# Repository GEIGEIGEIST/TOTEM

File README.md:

<picture align="center">
  <source media="(prefers-color-scheme: dark)" srcset="/docs/images/TOTEM_logo_dark.svg">
  <source media="(prefers-color-scheme: light)" srcset="/docs/images/TOTEM_logo_bright.svg">
  
</picture>

<h1 align="center">T O T E M</h1>

TOTEM is a 38 key column-staggered choc split keyboard. It is meant to be used with:
- **PCB v0.3:** [Seeed Studio XIAO nRF52840 BLE](https://www.seeedstudio.com/Seeed-XIAO-BLE-nRF52840-p-5201.html) or [XIAO RP2040](https://www.seeedstudio.com/XIAO-RP2040-v1-0-p-5026.html)
- **PCB v0.4:** [Seeed Studio XIAO nRF52840 BLE Plus](https://www.seeedstudio.com/Seeed-Studio-XIAO-nRF52840-Plus-p-6359.html) or [XIAO RP2350](https://www.seeedstudio.com/Seeed-XIAO-RP2350-p-5944.html)

It was created for the SEEED XIAO keyboard contest.\
[Here](https://www.hackster.io/geist/totem-a-tiny-splitkeyboard-with-splay-cb2e43) you can read about the process of making it.

***

## LAYOUT

***

## PCB

[Here](/PCB/) you can find the KiCad files and Gerbers for the TOTEM.

***

## CASE

You can use the TOTEM without a case, but [here](/case/) you can find one I made for it.

***

## BUILD GUIDE

The build guide for the TOTEM can be found [here](/docs/buildguide.md).

***

## FIRMWARE

[QMK (VIAL) precompiled](/firmware/QMK/) or [QMK (VIAL) source](/firmware/QMK/VIAL_source/) for the TOTEM (wired using the XIAO RP2040)\
[ZMK precompiled](/firmware/ZMK/) or [ZMK source (outdated)](https://github.com/GEIGEIGEIST/zmk-config-totem) for the TOTEM (wireless using the XIAO BLE)

***

## BUY

You can buy TOTEM kits and finished builds on [keeb.supply](https://keeb.supply/products/geist-totem) (based in Germany)

***

## PHOTOS

This is the TOTEM in a black resin case

\
\

This is the TOTEM with a black resin tenting bottom plate

\
[Video by *Wolfgang's Channel* showing the tenting system in action](https://youtu.be/rvM2BthjEI4?si=mTJVdPeZstshnDyo)

***

## CREDITS

### INSPIRATION

I've added the additional pinky key to make the TOTEM compatible with the layout boards like the [Balbuzard](https://github.com/brow/balbuzard) by [Tom Brow](https://github.com/brow) and the [Osprette](https://github.com/smores56/osprette) by [Sam Mohr](https://github.com/smores56) use, where you put the keybinding of the top left and right keys on an outer pinky key.

### HELP FIXING THINGS

People who helped me create this board and fix stuff

#### PCB
- [Marco "Bob"](https://github.com/GroooveBob)

#### CASE
- [Freya](https://github.com/freya-irl)
- [Bubbleology](https://github.com/bubbleology)

#### FIRMWARE
- [Cem Aksoylar](https://github.com/caksoylar)
- [Grinnie](https://github.com/regicidalplutophage)
- [Alaa Saad Mansour](https://github.com/AlaaSaadAbdo)
- [pekudzu](https://github.com/pekudzu)

If you build a TOTEM I would be pretty happy to see some pictures. And if you want to leave me a tip you can do this [here](https://ko-fi.com/geigeigeist) (but please don't feel pressured)

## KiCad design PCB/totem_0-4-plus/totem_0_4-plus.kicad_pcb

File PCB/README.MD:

# TOTEM PCB FILES

## MANUFACTURING

There are two versions available. Both fit the same [case](/case/README.MD), but require different microcontrollers.

### Version 0.3 (Standard)
Recommended for the standard **Seeed XIAO nRF52840** or **XIAO RP2040**.
- Download: [totem_0-3_gerbers.zip](/PCB/totem_0-3/totem_0-3_gerbers.zip/)

### Version 0.4 (Plus)
Tailored for the **Seeed XIAO nRF52840 Plus** and **XIAO RP2350**.
This version is **easier to solder** since there is a larger cutout. Also, the **battery pins are farther away** from the keyboard matrix pins, which should avoid shorts.
- Download: [totem_0-4-plus_gerbers.zip](/PCB/totem_0-4-plus/totem_0-4-plus_gerbers.zip)

---

If you want to get the PCB made you need to download the ZIP for your version and upload it to the website of the manufacture.
I can recommend [JLCPCB](https://jlcpcb.com/), [Seeed Fusion](https://www.seeedstudio.com/fusion_pcb.html) or [PCBway](https://www.pcbway.com/).
If you want the silkscreen in yellow [AllPCB](https://www.allpcb.com/online_pcb_quote_new.html) is a pretty affordable choice.

- download the ZIP file for your version
- upload the ZIP file to the website of the manufacturer.
- sometimes the Gerber preview from JLCPCB can't display the PCB, even when the files are fine. In this case use these dimensions: 258.7mm * 94.35mm
- PCB Thickness 1.6mm
- 2 layers
- PCB Qty as much as you like. One PCB is a full keyboard.
- PCB Color Black (or any other color you like)
- No impedance control
- Surface Finish HASL(with lead) if you want the easiest soldering experience or LeadFree HASL.
- Remove Order Number Yes

***

## CHECK PINOUT OR TRACES

If you only want to check the traces or see what is connected to which pin you can take a look at these graphics.
You can also take a look at the PDFs:
- **0.3:** [schematics](TOTEM_0-3_schematics.pdf) and [PCB](TOTEM_0-3_PCB.pdf)
- **0.4:** [schematics](TOTEM_0-3_schematics.pdf) and [PCB](TOTEM_0-4-plus-PCB.pdf)

***

***

## TAKE A DEEPER LOOK OR MODIFY 

You can download the project if you need to take a deeper look or modify something. You need the Open Source software [KiCad](https://www.kicad.org/) to open it.

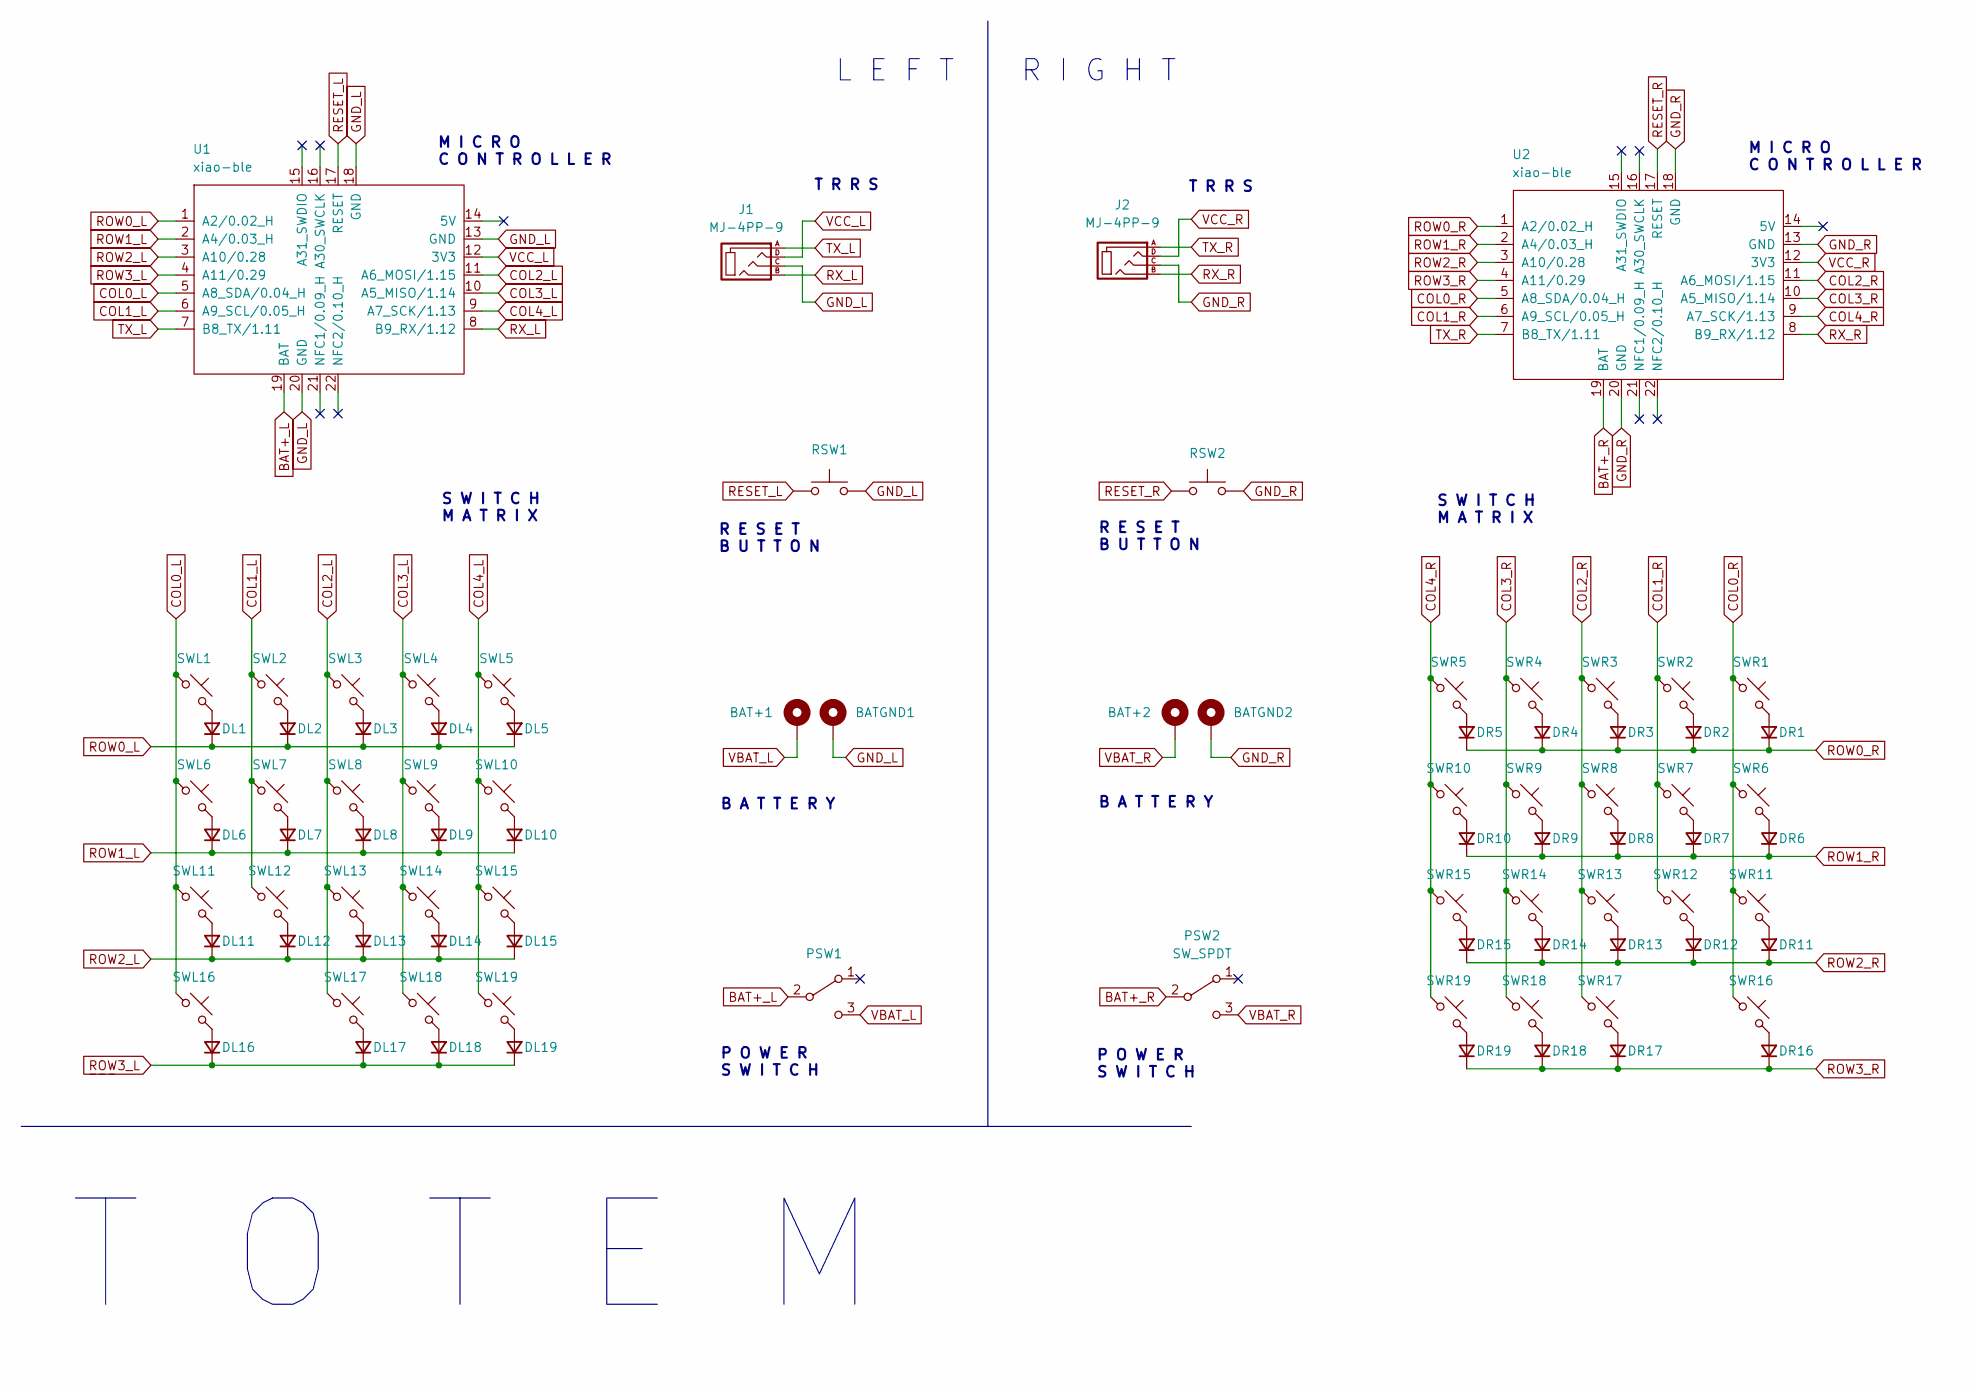
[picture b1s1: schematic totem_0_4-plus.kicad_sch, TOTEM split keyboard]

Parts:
BAT+1, BAT+2: +; BatteryPad
BATGND1, BATGND2: -; BatteryPad
DL1, DL2, DL3, DL4, DL5, DL6, DL7, DL8, DL9, DL10, DL11, DL12, DL13, DL14, DL15, DL16, DL17, DL18, DL19: D_Small; Diode_SOD123
DR1, DR2, DR3, DR4, DR5, DR6, DR7, DR8, DR9, DR10, DR11, DR12, DR13, DR14, DR15, DR16, DR17, DR18, DR19: D_Small; Diode_SOD123
J1, J2: MJ-4PP-9; MJ-4PP-9_1side
PSW1, PSW2: SW_SPDT; MSK12C02
RSW1, RSW2: SW_Push; SKHLLCA010
SWL1, SWL2, SWL3, SWL4, SWL5, SWL6, SWL7, SWL8, SWL9, SWL10, SWL11, SWL12, SWL13, SWL14, SWL15, SWL16, SWL17, SWL18, SWL19: SW_Push_45deg; Kailh_socket_PG1350_optional
SWR1, SWR2, SWR3, SWR4, SWR5, SWR6, SWR7, SWR8, SWR9, SWR10, SWR11, SWR12, SWR13, SWR14, SWR15, SWR16, SWR17, SWR18, SWR19: SW_Push_45deg; Kailh_socket_PG1350_optional
U1, U2: xiao-ble; XIAO-ble-plus

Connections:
BAT+_L: PSW1.2 (B), U1.19 (BAT)
BAT+_R: PSW2.2 (B), U2.19 (BAT)
COL0_L: SWL1.1, SWL6.1, SWL11.1, SWL16.1, U1.5 (A8_SDA/0.04_H)
COL0_R: SWR1.1, SWR6.1, SWR11.1, SWR16.1, U2.5 (A8_SDA/0.04_H)
COL1_L: SWL2.1, SWL7.1, SWL12.1, U1.6 (A9_SCL/0.05_H)
COL1_R: SWR2.1, SWR7.1, SWR12.1, U2.6 (A9_SCL/0.05_H)
COL2_L: SWL3.1, SWL8.1, SWL13.1, SWL17.1, U1.11 (A6_MOSI/1.15)
COL2_R: SWR3.1, SWR8.1, SWR13.1, SWR17.1, U2.11 (A6_MOSI/1.15)
COL3_L: SWL4.1, SWL9.1, SWL14.1, SWL18.1, U1.10 (A5_MISO/1.14)
COL3_R: SWR4.1, SWR9.1, SWR14.1, SWR18.1, U2.10 (A5_MISO/1.14)
COL4_L: SWL5.1, SWL10.1, SWL15.1, SWL19.1, U1.9 (A7_SCK/1.13)
COL4_R: SWR5.1, SWR10.1, SWR15.1, SWR19.1, U2.9 (A7_SCK/1.13)
GND_L: BATGND1.1 (1_1), J1.C, RSW1.2, U1.13 (GND), U1.18 (GND), U1.20 (GND)
GND_R: BATGND2.1 (1_1), J2.C, RSW2.2, U2.13 (GND), U2.18 (GND), U2.20 (GND)
unnamed: DL1.2 (A), SWL1.2
unnamed: DL2.2 (A), SWL2.2
unnamed: DL3.2 (A), SWL3.2
unnamed: DL4.2 (A), SWL4.2
unnamed: DL5.2 (A), SWL5.2
unnamed: DL6.2 (A), SWL6.2
unnamed: DL7.2 (A), SWL7.2
unnamed: DL8.2 (A), SWL8.2
unnamed: DL9.2 (A), SWL9.2
unnamed: DL10.2 (A), SWL10.2
unnamed: DL11.2 (A), SWL11.2
unnamed: DL12.2 (A), SWL12.2
unnamed: DL13.2 (A), SWL13.2
unnamed: DL14.2 (A), SWL14.2
unnamed: DL15.2 (A), SWL15.2
unnamed: DL16.2 (A), SWL16.2
unnamed: DL17.2 (A), SWL17.2
unnamed: DL18.2 (A), SWL18.2
unnamed: DL19.2 (A), SWL19.2
unnamed: DR1.2 (A), SWR1.2
unnamed: DR2.2 (A), SWR2.2
unnamed: DR3.2 (A), SWR3.2
unnamed: DR4.2 (A), SWR4.2
unnamed: DR5.2 (A), SWR5.2
unnamed: DR6.2 (A), SWR6.2
unnamed: DR7.2 (A), SWR7.2
unnamed: DR8.2 (A), SWR8.2
unnamed: DR9.2 (A), SWR9.2
unnamed: DR10.2 (A), SWR10.2
unnamed: DR11.2 (A), SWR11.2
unnamed: DR12.2 (A), SWR12.2
unnamed: DR13.2 (A), SWR13.2
unnamed: DR14.2 (A), SWR14.2
unnamed: DR15.2 (A), SWR15.2
unnamed: DR16.2 (A), SWR16.2
unnamed: DR17.2 (A), SWR17.2
unnamed: DR18.2 (A), SWR18.2
unnamed: DR19.2 (A), SWR19.2
RESET_L: RSW1.1, U1.17 (RESET)
RESET_R: RSW2.1, U2.17 (RESET)
ROW0_L: DL1.1 (K), DL2.1 (K), DL3.1 (K), DL4.1 (K), DL5.1 (K), U1.1 (A2/0.02_H)
ROW0_R: DR1.1 (K), DR2.1 (K), DR3.1 (K), DR4.1 (K), DR5.1 (K), U2.1 (A2/0.02_H)
ROW1_L: DL6.1 (K), DL7.1 (K), DL8.1 (K), DL9.1 (K), DL10.1 (K), U1.2 (A4/0.03_H)
ROW1_R: DR6.1 (K), DR7.1 (K), DR8.1 (K), DR9.1 (K), DR10.1 (K), U2.2 (A4/0.03_H)
ROW2_L: DL11.1 (K), DL12.1 (K), DL13.1 (K), DL14.1 (K), DL15.1 (K), U1.3 (A10/0.28)
ROW2_R: DR11.1 (K), DR12.1 (K), DR13.1 (K), DR14.1 (K), DR15.1 (K), U2.3 (A10/0.28)
ROW3_L: DL16.1 (K), DL17.1 (K), DL18.1 (K), DL19.1 (K), U1.4 (A11/0.29)
ROW3_R: DR16.1 (K), DR17.1 (K), DR18.1 (K), DR19.1 (K), U2.4 (A11/0.29)
RX_L: J1.B, U1.8 (B9_RX/1.12)
RX_R: J2.B, U2.8 (B9_RX/1.12)
TX_L: J1.A, U1.7 (B8_TX/1.11)
TX_R: J2.A, U2.7 (B8_TX/1.11)
VBAT_L: BAT+1.1 (1_1), PSW1.3 (C)
VBAT_R: BAT+2.1 (1_1), PSW2.3 (C)
VCC_L: J1.D, U1.12 (3V3)
VCC_R: J2.D, U2.12 (3V3)

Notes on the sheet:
M I C R O C O N T R O L L E R
T R R S
R E S E T B U T T O N
S W I T C H M A T R I X
P O W E R S W I T C H
T O T E M
B A T T E R Y
R I G H T
L E F T

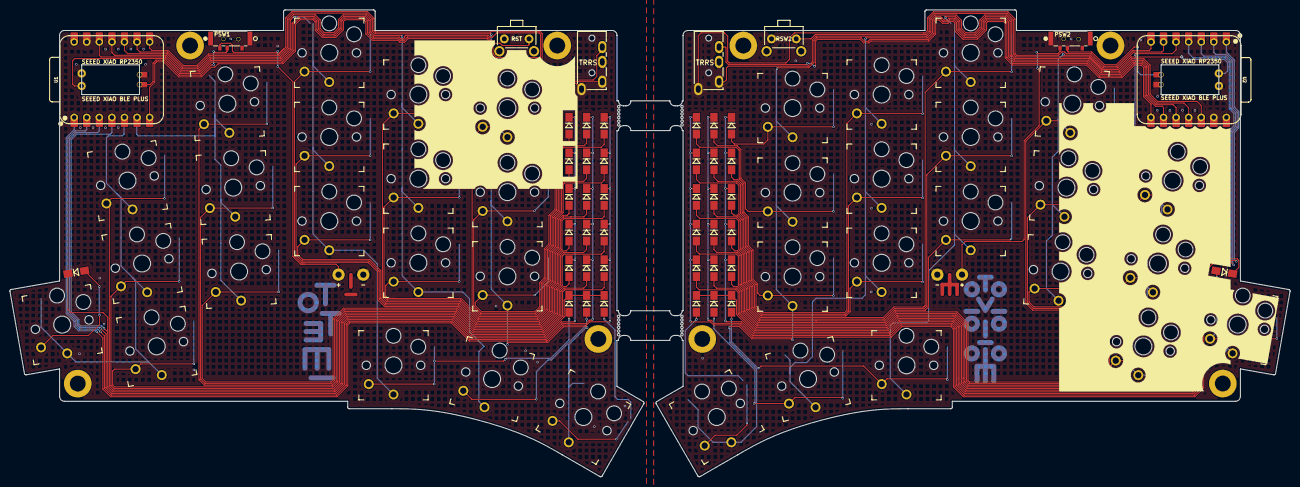
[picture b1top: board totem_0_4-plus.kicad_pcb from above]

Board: 2 copper layers, 258.7 x 94.4 mm, 88 parts (0 on the bottom side), 70 nets.

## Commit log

2022-07-28 update logo
2022-11-03 Update layout
2022-11-03 case render
2022-11-03 buildguide
2022-11-04 add photos
2022-11-04 update photo
2022-11-04 readme
2022-11-04 readmes
2022-11-04 case images
2022-11-04 case documentation
2022-11-04 add case files
2022-11-06 update traces
2022-11-06 layout
2022-11-07 update buildguide
2022-11-10 schematic and PCB as PDF
2022-11-10 Add KiCad files and gerbers
2022-11-13 add case options
2022-12-12 Fixed small typographical error
    without TRRS cutout == wireless version, not wired.
2022-12-20 update case files
2023-04-14 Fix grammar
    Language r hard
2023-05-17 TOTEMX 0.1
    Hello.
    Can be useful. Totally untested.
    Stay safe.
2024-05-21 added tenting case options
2024-05-22 added pictures to main readme
2024-05-22 added more info and pictures to the case readme
2024-05-22 fixed typo and improved linkage
2024-06-01 added usb tenting bottom plate
2024-06-01 removed top piece from stl bottom plates
2024-06-01 renamed usb bottom plate stl file
2024-09-25 Update TOTEM_traces.svg: Add Missing Diode numbers
2024-09-25 Update README.md
    added link to wolfgang's video
2024-10-13 add precompiled firmware
2024-11-01 Remove TRRS & add USB C port to case
2024-11-01 Fillet sharp outer edges of top cases
2024-11-01 Remove TRRS connector indents from BLE bottom cases
2024-11-13 Update buildguide.md
    Update product name to align with the new name on the manufacture's website, adding hyperlinks for people who want to learn more details
2024-11-13 Update README.md
    Update the product name to align with the new name from the manufacture, adding hyperlinks for people who want to explore more
2024-12-08 fix standoff hole near the RST button (9mm)
2024-12-08 update readme on availability
2024-12-08 add VIAL source
2024-12-08 fix video link
2024-12-08 Remove outdated qmk version
2024-12-28 Create a hybrid case with both ble and usb component holes
2024-12-31 Update rules.mk
    Added: SPLIT_KEYBOARD = yes
2025-03-12 Update README.md
    Clarify shipping info
2025-08-14 totem case optimized for CNC
2025-08-23 Add a transport case
